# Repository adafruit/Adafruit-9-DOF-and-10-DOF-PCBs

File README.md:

# PCB for the Adafruit 9-DOF and 10-DOF Breakout boards

__Format is EagleCAD schematic and board layout__

* [Adafruit 9-DOF IMU Breakout - L3GD20H + LSM303](https://www.adafruit.com/product/1714)
* [Adafruit 10-DOF IMU Breakout - L3GD20H + LSM303 + BMP180](https://www.adafruit.com/product/1604)

This inertial-measurement-unit combines 2 of the best quality sensors available on the market to give you 9 axes of data: 3 axes of accelerometer data, 3 axes gyroscopic, and 3 axes magnetic (compass). We tested many different 'combination' sensors and found these were the best value, with stable and reliable readings.

The L3DG20H gyroscope + LSM303DLHC accelerometer/compass sensors are all on one breakout here, to save you space and money. Since all of them use I2C, you can communicate with all of them using only two wires. Most customers will be pretty happy with just the plain I2C interfacing, but we also break out the 'data ready' and 'interrupt' pins, so advanced users can interface with if they choose. A 3V regulator with reverse-polarity protection means you don't have to worry about frying the boards by accident. There's level shifting circuitry so the IMU can be used with 3 or 5V logic boards. And check out those mounting holes! You can securely attach this board to your rocket, robot, art project.

Each order comes with one assembled and tested 9DOF breakout board and a small piece of header.

Since this is a combination of 2 different breakouts, we suggest visiting those pages for much more information: [L3GD20H](http://www.adafruit.com/products/1032) and the [LSM303](http://www.adafruit.com/products/1120), but here are some quick stats:

- L3GD20H 3-axis gyroscope: ?250, ?500, or ?2000 degree-per-second scale
- LSM303 3-axis compass: ?1.3 to ?8.1 gauss magnetic field scale
- LSM303 3-axis accelerometer: ?2g/?4g/?8g/?16g selectable scale

[Our tutorial for this board is over on learn, including example Arduino code that will auto-calculate tilt & heading](http://learn.adafruit.com/adafruit-9-dof-imu-breakout).

## License

Adafruit invests time and resources providing this open source design, 
please support Adafruit and open-source hardware by purchasing 
products from Adafruit!

Designed by Adafruit Industries.  
Creative Commons Attribution, Share-Alike license, check license.txt for more information
All text above must be included in any redistribution

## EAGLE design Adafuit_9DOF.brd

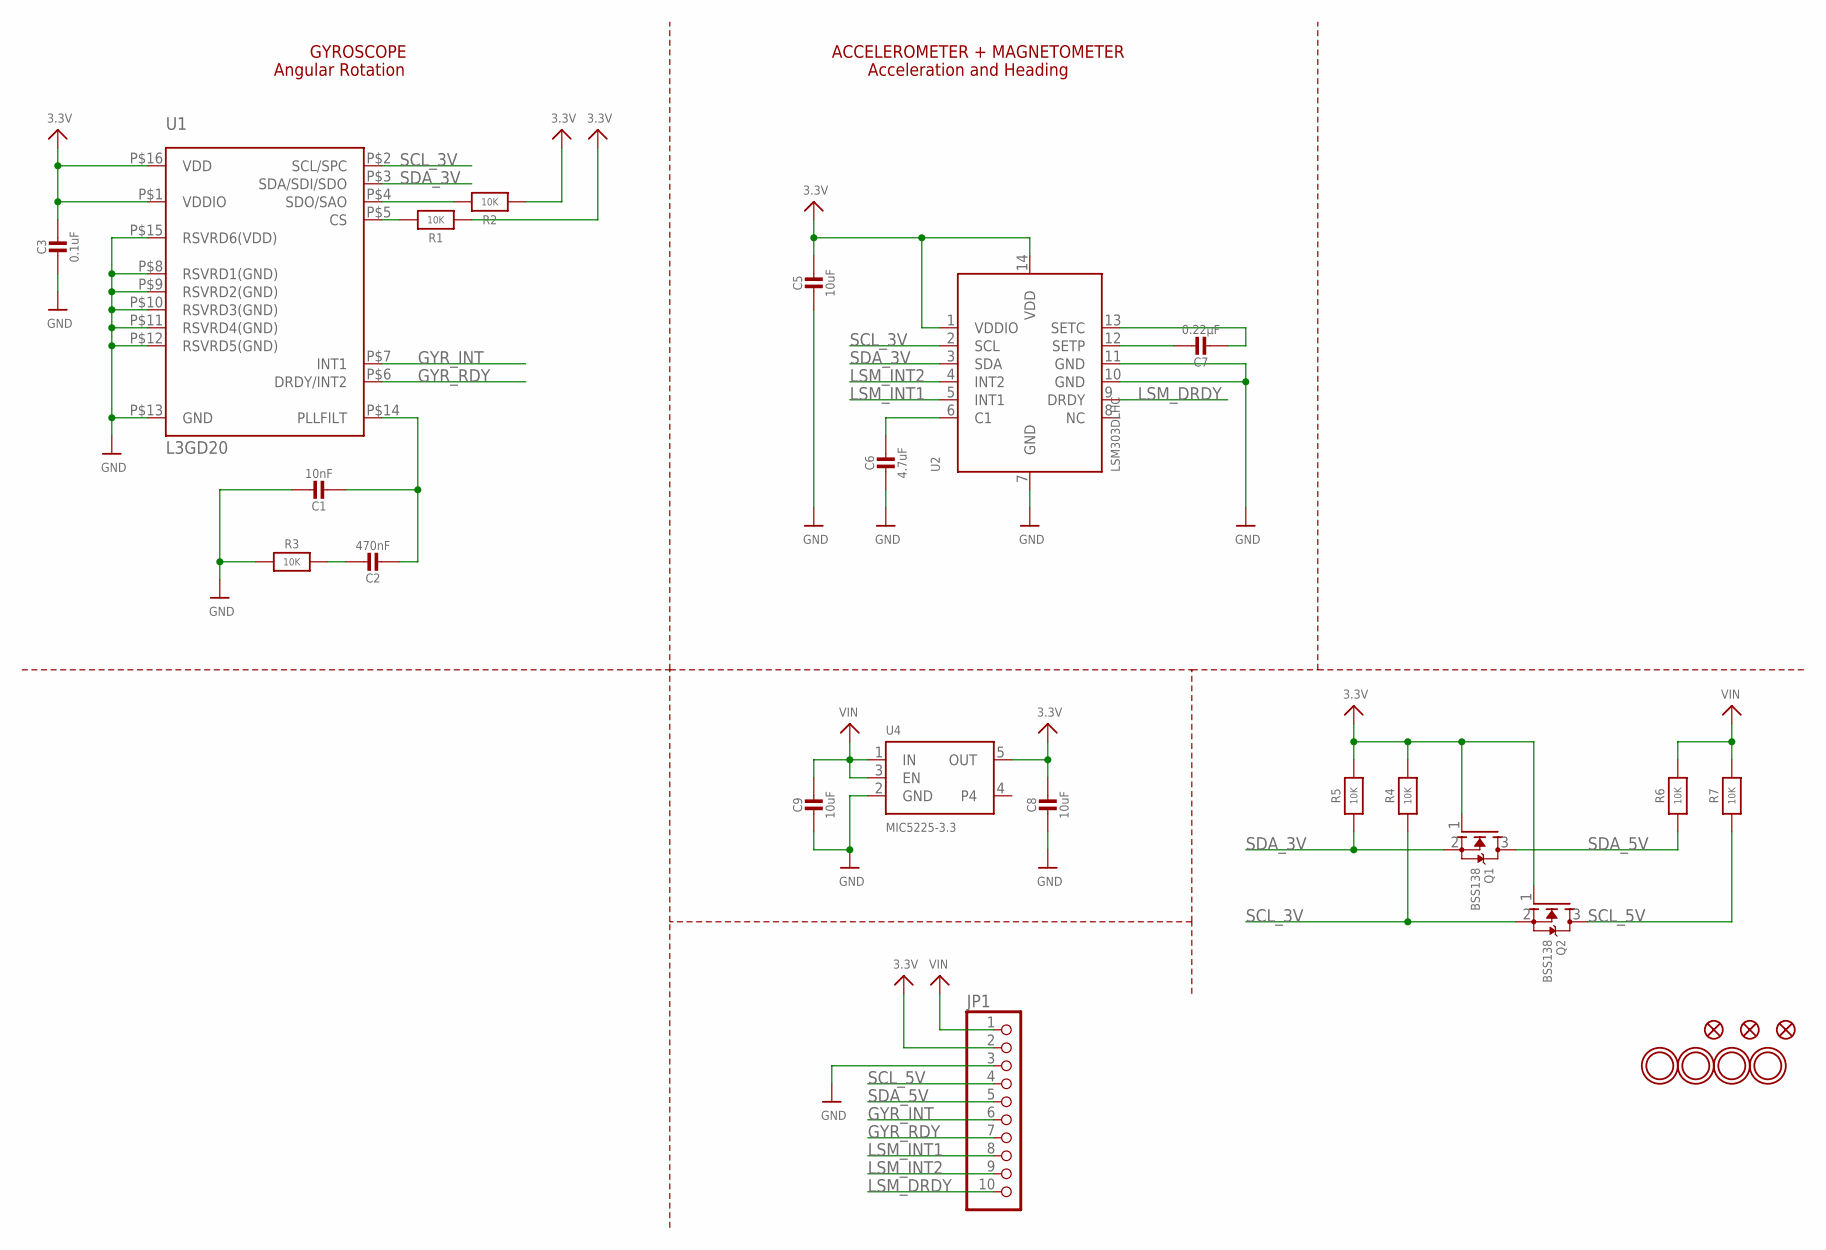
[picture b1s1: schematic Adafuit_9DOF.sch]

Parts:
C1: 10nF; _0805MP
C2: 470nF; _0805MP
C3: 0.1uF; _0805MP
C5, C8, C9: 10uF; _0805MP
C6: 4.7uF; _0805MP
C7: 0.22µF; _0805MP
FID1, FID2, FID3: FIDUCIAL""; FIDUCIAL_1MM
JP1: HEADER-1X10ROUND; 1X10_ROUND
Q1, Q2: BSS138; SOT23-WIDE
R1, R2, R3, R4, R5, R6, R7: 10K; _0805MP
U1: L3GD20; L3G4200D_LGA16L
U2: LSM303DLHC; LGA14
U4: MIC5225-3.3; SOT23-5
U$28, U$29, U$30, U$31: MOUNTINGHOLE2.5_THICK; MOUNTINGHOLE_2.5_PLATED_THICK

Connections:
3.3V: C3.1, C5.1, C8.1, JP1.2, Q1.1 (G), Q2.1 (G), R1.1, R2.1, R4.2, R5.2, U1.P$1 (VDDIO), U1.P$16 (VDD), U2.1 (VDDIO), U2.14 (VDD), U4.5 (OUT)
GND: C1.1, C3.2, C5.2, C6.2, C8.2, C9.2, JP1.3, R3.1, U1.P$8 (RSVRD1(GND)), U1.P$9 (RSVRD2(GND)), U1.P$10 (RSVRD3(GND)), U1.P$11 (RSVRD4(GND)), U1.P$12 (RSVRD5(GND)), U1.P$13 (GND), U1.P$15 (RSVRD6(VDD)), U2.7 (GND), U2.10 (GND), U2.11 (GND), U4.2 (GND)
GYR_INT: JP1.6, U1.P$7 (INT1)
GYR_RDY: JP1.7, U1.P$6 (DRDY/INT2)
LSM_DRDY: JP1.10, U2.9 (DRDY)
LSM_INT1: JP1.8, U2.5 (INT1)
LSM_INT2: JP1.9, U2.4 (INT2)
unnamed: R1.2, U1.P$5 (CS)
unnamed: R2.2, U1.P$4 (SDO/SAO)
unnamed: C2.1, R3.2
unnamed: C1.2, C2.2, U1.P$14 (PLLFILT)
unnamed: C7.1, U2.12 (SETP)
unnamed: C6.1, U2.6 (C1)
unnamed: C7.2, U2.13 (SETC)
SCL_3V: Q2.2 (S), R4.1, U1.P$2 (SCL/SPC), U2.2 (SCL)
SCL_5V: JP1.4, Q2.3 (D), R7.1
SDA_3V: Q1.2 (S), R5.1, U1.P$3 (SDA/SDI/SDO), U2.3 (SDA)
SDA_5V: JP1.5, Q1.3 (D), R6.1
VIN: C9.1, JP1.1, R6.2, R7.2, U4.1 (IN), U4.3 (EN)

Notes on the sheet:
GYROSCOPE
Angular Rotation
ACCELEROMETER + MAGNETOMETER
Acceleration and Heading

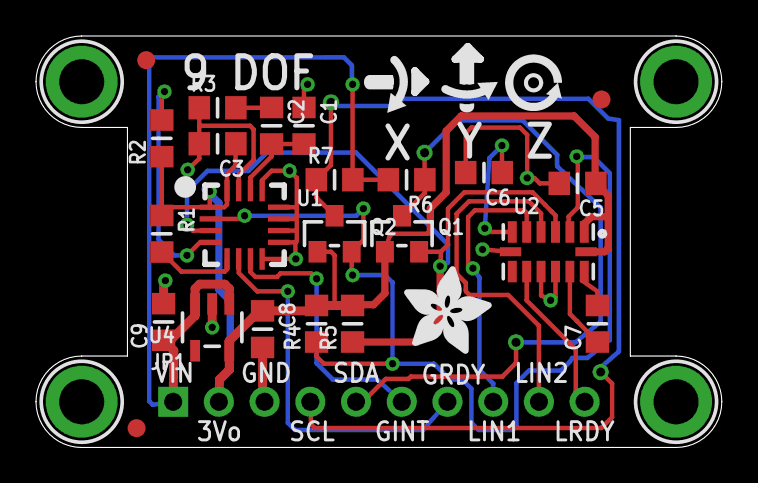
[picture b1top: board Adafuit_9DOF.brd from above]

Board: 2 copper layers, 38.1 x 22.9 mm, 31 parts (1 on the bottom side), 19 nets.

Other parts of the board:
U$8: ADAFRUIT_5MM
U$25: SYMBOL_GYROXYZ_10MM
U$26: ADAFRUIT_TEXT_20MM

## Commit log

2014-06-10 init
2014-06-10 url fix
2019-05-16 readme + image + license
2019-05-16 readme update

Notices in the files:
parts and their libraries:
microbuilder: This work is placed in the public domain, and may be freely used for commercial and non-commercial work with the following conditions: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
